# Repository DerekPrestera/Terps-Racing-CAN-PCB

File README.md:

# Terps-Racing-CAN-PCB
A custom Arduino Uno Shield to construct a CAN network data collection system

This board is the basis for a CAN network based sensor system for Terps Racing vehicles. It is a shield for Arduino uno that allows the Arduino to communicated on a CAN netowrk with the MCP2515 CAN to SPI chip and read analog sensor data with 12-bit resolution with the MCP3208 ADC chip. This turns the Arduino into a data collection CAN Node that can be placed right next to the location of a sensor and transmit its reading to the vehicle's CAN bus for logging, telemetry, or possibly use by data-driven active components elsewhere on the vehicle.

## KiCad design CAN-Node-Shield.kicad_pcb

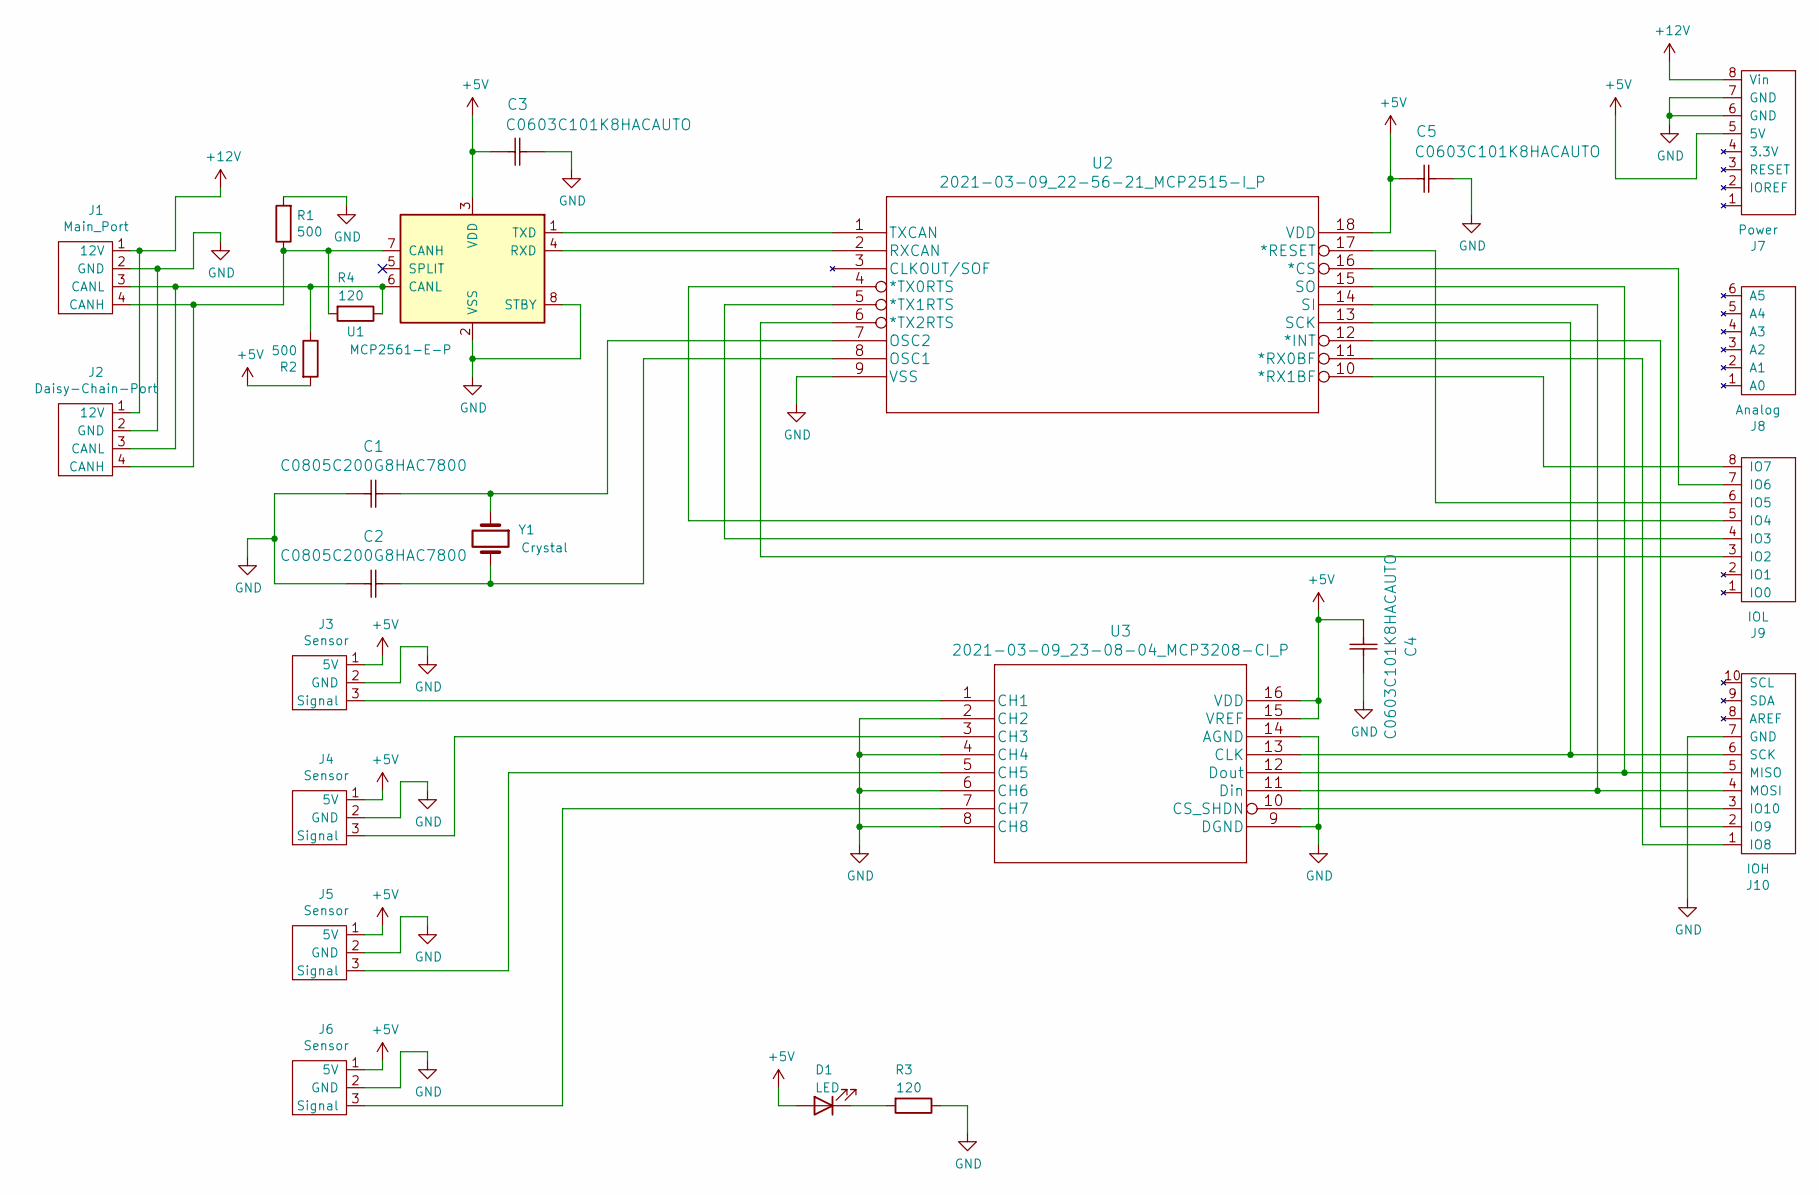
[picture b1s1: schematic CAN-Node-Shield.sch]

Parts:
C1, C2: C0805C200G8HAC7800; C_Rect_L7.0mm_W2.5mm_P5.00mm
C3, C4, C5: C0603C101K8HACAUTO; C_Rect_L4.0mm_W2.5mm_P2.50mm
D1: LED; LED_D5.0mm_FlatTop
J1: Main_Port; PinHeader_1x04_P2.54mm_Vertical
J2: Daisy-Chain-Port; PinHeader_1x04_P2.54mm_Vertical
J3, J4, J5, J6: Sensor; PinHeader_1x03_P2.54mm_Vertical
J7: Power; PinSocket_1x08_P2.54mm_Vertical
J8: Analog; PinSocket_1x06_P2.54mm_Vertical
J9: IOL; PinSocket_1x08_P2.54mm_Vertical
J10: IOH; PinSocket_1x10_P2.54mm_Vertical
R1, R2: 500; R_Axial_DIN0207_L6.3mm_D2.5mm_P10.16mm_Horizontal
R3, R4: 120; R_Axial_DIN0207_L6.3mm_D2.5mm_P10.16mm_Horizontal
U1: MCP2561-E-P; DIP-8_W7.62mm
U2: 2021-03-09_22-56-21_MCP2515-I_P; DIP-18_W7.62mm
U3: 2021-03-09_23-08-04_MCP3208-CI_P; DIP-16_W7.62mm
Y1: Crystal; Crystal_HC49-U_Vertical

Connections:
+5V: C3.1, C4.1, C5.1, D1.2 (A), J3.1 (5V), J4.1 (5V), J5.1 (5V), J6.1 (5V), J7.5 (5V), R2.2, U1.3 (VDD), U2.18 (VDD), U3.15 (VREF), U3.16 (VDD)
+12V: J1.1 (12V), J2.1 (12V), J7.8 (Vin)
GND: C1.1, C2.1, C3.2, C4.2, C5.2, J1.2 (GND), J2.2 (GND), J3.2 (GND), J4.2 (GND), J5.2 (GND), J6.2 (GND), J7.6 (GND), J7.7 (GND), J10.7 (GND), R1.2, R3.1, U1.2 (VSS), U1.8 (STBY), U2.9 (VSS), U3.2 (CH2), U3.4 (CH4), U3.6 (CH6), U3.8 (CH8), U3.9 (DGND), U3.14 (AGND)
unnamed: C1.2, U2.7 (OSC2), Y1.1
unnamed: C2.2, U2.8 (OSC1), Y1.2
unnamed: D1.1 (K), R3.2
unnamed: J1.3 (CANL), J2.3 (CANL), R2.1, R4.1, U1.6 (CANL)
unnamed: J1.4 (CANH), J2.4 (CANH), R1.1, R4.2, U1.7 (CANH)
unnamed: J3.3 (Signal), U3.1 (CH1)
unnamed: J4.3 (Signal), U3.3 (CH3)
unnamed: J5.3 (Signal), U3.5 (CH5)
unnamed: J6.3 (Signal), U3.7 (CH7)
unnamed: J9.3 (IO2), U2.6 (*TX2RTS)
unnamed: J9.4 (IO3), U2.5 (*TX1RTS)
unnamed: J9.5 (IO4), U2.4 (*TX0RTS)
unnamed: J9.6 (IO5), U2.17 (*RESET)
unnamed: J9.7 (IO6), U2.16 (*CS)
unnamed: J9.8 (IO7), U2.10 (*RX1BF)
unnamed: J10.1 (IO8), U2.11 (*RX0BF)
unnamed: J10.2 (IO9), U2.12 (*INT)
unnamed: J10.3 (IO10), U3.10 (CS_SHDN)
unnamed: J10.4 (MOSI), U2.14 (SI), U3.11 (Din)
unnamed: J10.5 (MISO), U2.15 (SO), U3.12 (Dout)
unnamed: J10.6 (SCK), U2.13 (SCK), U3.13 (CLK)
unnamed: U1.1 (TXD), U2.1 (TXCAN)
unnamed: U1.4 (RXD), U2.2 (RXCAN)

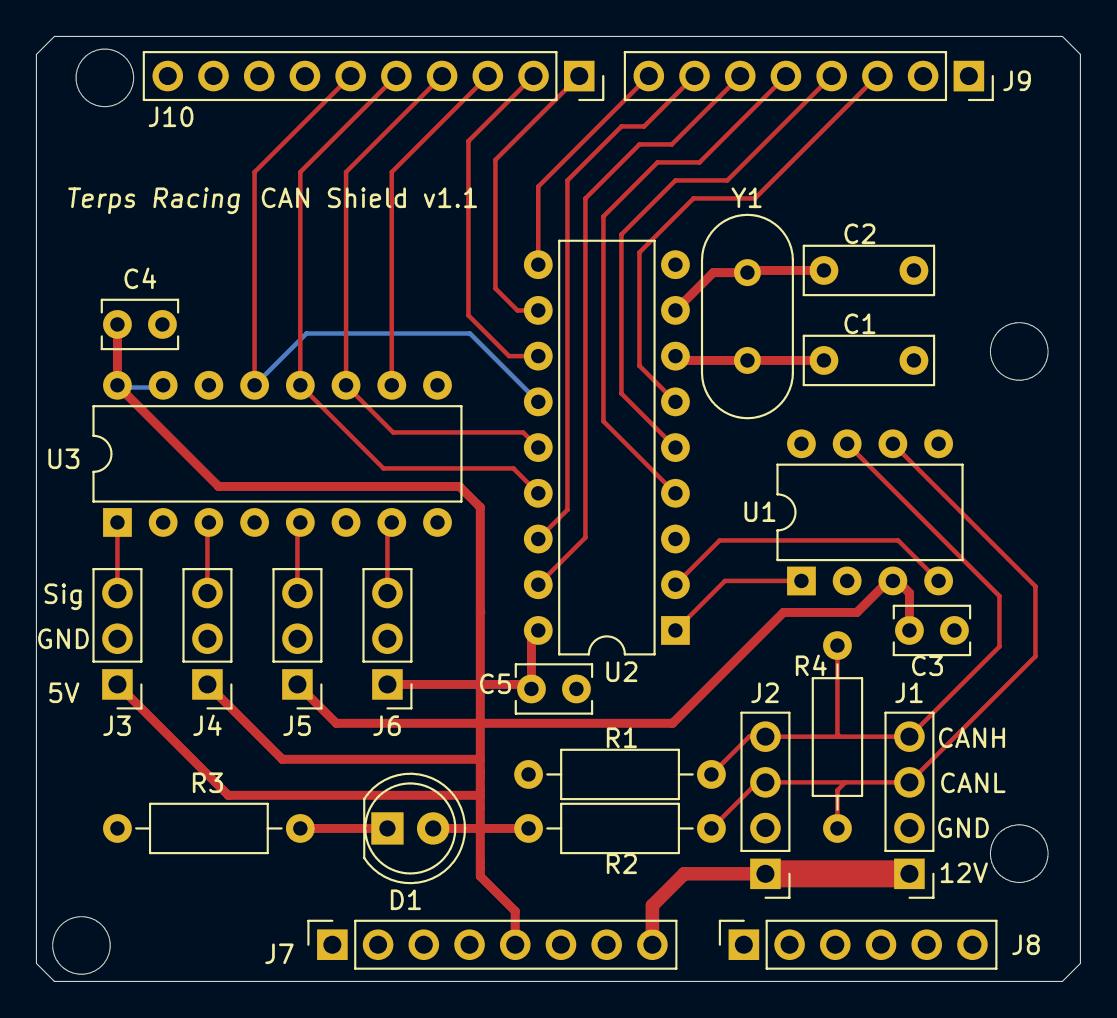
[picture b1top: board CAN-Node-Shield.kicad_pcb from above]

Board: 2 copper layers, 58.0 x 52.5 mm, 24 parts (0 on the bottom side), 26 nets.

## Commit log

2022-09-15 Re-upload to dedicated repository
